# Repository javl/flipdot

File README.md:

### Work in progress! This project is not completed yet!

# Flipdot
A controller for flipdot displays using the FP2800A BROSE chip. The schematic is heavily based on / pretty much a clone of [flippie](https://github.com/545ch4/flippie). See the flippie repo for a great explaination of how the BROSE displays are controlled.

Changes I have made / are planning on making are:

  * [X] Made in the open source Kicad instead of Eagle
  * [X] Replaced the TBD62783A which a A2982 as it seams easier to find
  * [ ] On-board power conversion instead of needing separate inputs for 3.3V, 5V and 24V

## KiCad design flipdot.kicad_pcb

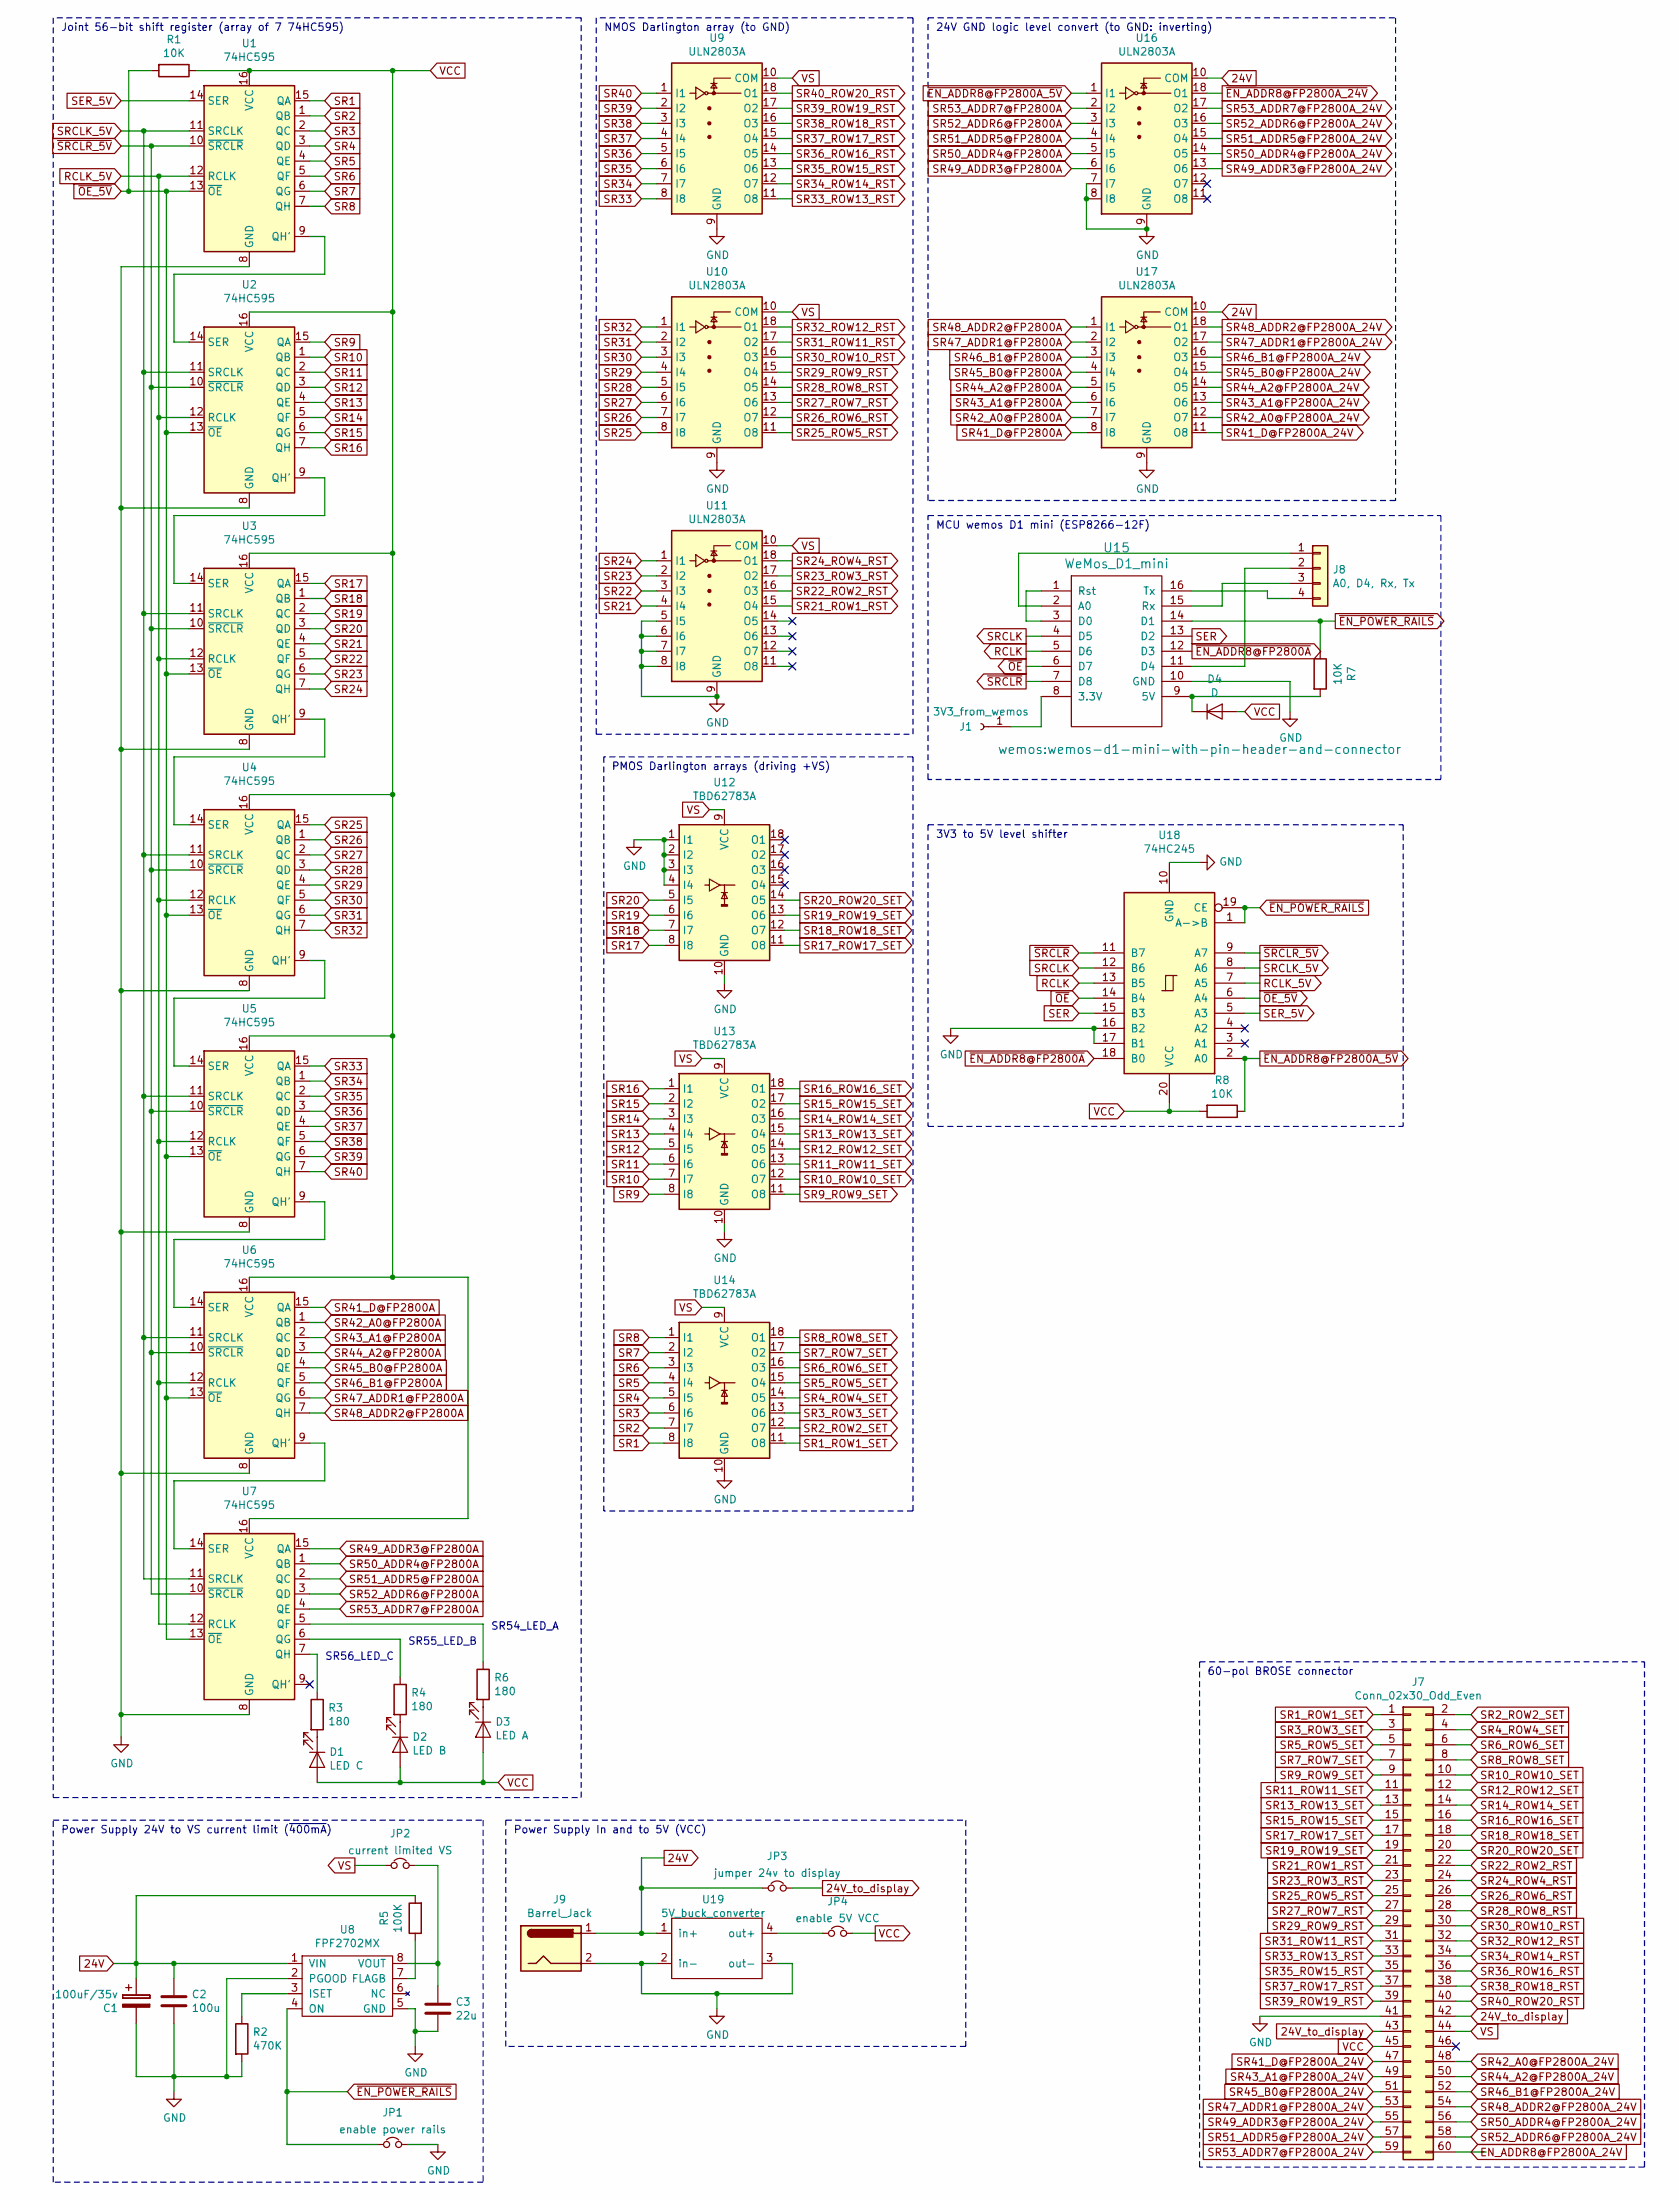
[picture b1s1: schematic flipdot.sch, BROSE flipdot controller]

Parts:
C1: 100uF/35v; CP_Elec_6.3x7.7
C2: 100u; CP_Radial_D6.3mm_P2.50mm
C3: 22u; CP_Radial_D5.0mm_P2.00mm
D1: LED C; LED_0805_2012Metric
D2: LED B; LED_0805_2012Metric
D3: LED A; LED_0805_2012Metric
D4: D; D_A-405_P7.62mm_Horizontal
J1: 3V3_from_wemos; PinHeader_1x01_P2.54mm_Vertical
J7: Conn_02x30_Odd_Even; PinHeader_2x30_P2.54mm_Vertical
J8: A0, D4, Rx, Tx; PinHeader_1x04_P2.54mm_Vertical
J9: Barrel_Jack; BarrelJack_Wuerth_6941xx301002
JP1: enable power rails; PinHeader_1x02_P2.54mm_Vertical
JP2: current limited VS; PinHeader_1x02_P2.54mm_Vertical
JP3: jumper 24v to display; PinHeader_1x02_P2.54mm_Vertical
JP4: enable 5V VCC; PinHeader_1x02_P2.54mm_Vertical
R1, R7, R8: 10K; R_0805_2012Metric
R2: 470K; R_0603_1608Metric
R3, R4, R6: 180; R_0603_1608Metric
R5: 100K; R_0603_1608Metric
U1, U2, U3, U4, U5, U6, U7: 74HC595; SOIC-16_3.9x9.9mm_P1.27mm
U8: FPF2702MX; SOIC-8_3.9x4.9mm_P1.27mm
U9, U10, U11, U16, U17: ULN2803A; SOIC-18W_7.5x11.6mm_P1.27mm
U12, U13, U14: TBD62783A; SOIC-20W_7.5x12.8mm_P1.27mm
U15: WeMos_D1_mini; wemos-d1-mini-with-pin-header-and-connector
U18: 74HC245; SO-20_12.8x7.5mm_P1.27mm
U19: 5V_buck_converter; 5v_buck_converter

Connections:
24V: C1.1, C2.1, J9.1, JP3.1, R5.2, U8.1 (VIN), U16.10 (COM), U17.10 (COM), U19.1 (in+)
24V_to_display: J7.42, J7.43, JP3.2
unnamed: C3.1, JP2.2, U8.8 (VOUT)
unnamed: D1.1 (K), R3.2
unnamed: D2.1 (K), R4.2
unnamed: D3.1 (K), R6.2
unnamed: D4.1 (K), R7.2, U15.9 (5V)
unnamed: J1.1, U15.8 (3.3V)
unnamed: J8.1, U15.2 (A0)
unnamed: J8.2, U15.11 (D4)
unnamed: J8.3, U15.15 (Rx)
unnamed: J8.4, U15.16 (Tx)
unnamed: JP4.1, U19.4 (out+)
unnamed: R2.1, U8.3 (ISET)
unnamed: R3.1, U7.7 (QH)
unnamed: R4.1, U7.6 (QG)
unnamed: R5.1, U8.7 (FLAGB)
unnamed: R6.1, U7.5 (QF)
unnamed: U1.9 (QH'), U2.14 (SER)
unnamed: U2.9 (QH'), U3.14 (SER)
unnamed: U3.9 (QH'), U4.14 (SER)
unnamed: U4.9 (QH'), U5.14 (SER)
unnamed: U5.9 (QH'), U6.14 (SER)
unnamed: U6.9 (QH'), U7.14 (SER)
unnamed: U15.1 (Rst), U15.3 (D0)
RCLK: U15.5 (D6), U18.13 (B5)
RCLK_5V: U1.12 (RCLK), U2.12 (RCLK), U3.12 (RCLK), U4.12 (RCLK), U5.12 (RCLK), U6.12 (RCLK), U7.12 (RCLK), U18.7 (A5)
SER: U15.13 (D2), U18.15 (B3)
SER_5V: U1.14 (SER), U18.5 (A3)
SR1: U1.15 (QA), U14.8 (I8)
SR1_ROW1_SET: J7.1, U14.11 (O8)
SR2: U1.1 (QB), U14.7 (I7)
SR2_ROW2_SET: J7.2, U14.12 (O7)
SR3: U1.2 (QC), U14.6 (I6)
SR3_ROW3_SET: J7.3, U14.13 (O6)
SR4: U1.3 (QD), U14.5 (I5)
SR4_ROW4_SET: J7.4, U14.14 (O5)
SR5: U1.4 (QE), U14.4 (I4)
SR5_ROW5_SET: J7.5, U14.15 (O4)
SR6: U1.5 (QF), U14.3 (I3)
SR6_ROW6_SET: J7.6, U14.16 (O3)
SR7: U1.6 (QG), U14.2 (I2)
SR7_ROW7_SET: J7.7, U14.17 (O2)
SR8: U1.7 (QH), U14.1 (I1)
SR8_ROW8_SET: J7.8, U14.18 (O1)
SR9: U2.15 (QA), U13.8 (I8)
SR9_ROW9_SET: J7.9, U13.11 (O8)
SR10: U2.1 (QB), U13.7 (I7)
SR10_ROW10_SET: J7.10, U13.12 (O7)
SR11: U2.2 (QC), U13.6 (I6)
SR11_ROW11_SET: J7.11, U13.13 (O6)
SR12: U2.3 (QD), U13.5 (I5)
SR12_ROW12_SET: J7.12, U13.14 (O5)
SR13: U2.4 (QE), U13.4 (I4)
SR13_ROW13_SET: J7.13, U13.15 (O4)
SR14: U2.5 (QF), U13.3 (I3)
SR14_ROW14_SET: J7.14, U13.16 (O3)
SR15: U2.6 (QG), U13.2 (I2)
SR15_ROW15_SET: J7.15, U13.17 (O2)
SR16: U2.7 (QH), U13.1 (I1)
SR16_ROW16_SET: J7.16, U13.18 (O1)
SR17: U3.15 (QA), U12.8 (I8)
SR17_ROW17_SET: J7.17, U12.11 (O8)
SR18: U3.1 (QB), U12.7 (I7)
SR18_ROW18_SET: J7.18, U12.12 (O7)
SR19: U3.2 (QC), U12.6 (I6)
SR19_ROW19_SET: J7.19, U12.13 (O6)
SR20: U3.3 (QD), U12.5 (I5)
SR20_ROW20_SET: J7.20, U12.14 (O5)
SR21: U3.4 (QE), U11.4 (I4)
SR21_ROW1_RST: J7.21, U11.15 (O4)
SR22: U3.5 (QF), U11.3 (I3)
SR22_ROW2_RST: J7.22, U11.16 (O3)
SR23: U3.6 (QG), U11.2 (I2)
SR23_ROW3_RST: J7.23, U11.17 (O2)
SR24: U3.7 (QH), U11.1 (I1)
SR24_ROW4_RST: J7.24, U11.18 (O1)
SR25: U4.15 (QA), U10.8 (I8)
SR25_ROW5_RST: J7.25, U10.11 (O8)
SR26: U4.1 (QB), U10.7 (I7)
SR26_ROW6_RST: J7.26, U10.12 (O7)
SR27: U4.2 (QC), U10.6 (I6)
SR27_ROW7_RST: J7.27, U10.13 (O6)
SR28: U4.3 (QD), U10.5 (I5)
SR28_ROW8_RST: J7.28, U10.14 (O5)
SR29: U4.4 (QE), U10.4 (I4)
SR29_ROW9_RST: J7.29, U10.15 (O4)
SR30: U4.5 (QF), U10.3 (I3)
SR30_ROW10_RST: J7.30, U10.16 (O3)
SR31: U4.6 (QG), U10.2 (I2)
SR31_ROW11_RST: J7.31, U10.17 (O2)
SR32: U4.7 (QH), U10.1 (I1)
SR32_ROW12_RST: J7.32, U10.18 (O1)
SR33: U5.15 (QA), U9.8 (I8)
SR33_ROW13_RST: J7.33, U9.11 (O8)
SR34: U5.1 (QB), U9.7 (I7)
SR34_ROW14_RST: J7.34, U9.12 (O7)
SR35: U5.2 (QC), U9.6 (I6)
SR35_ROW15_RST: J7.35, U9.13 (O6)
SR36: U5.3 (QD), U9.5 (I5)
SR36_ROW16_RST: J7.36, U9.14 (O5)
SR37: U5.4 (QE), U9.4 (I4)
SR37_ROW17_RST: J7.37, U9.15 (O4)
SR38: U5.5 (QF), U9.3 (I3)
SR38_ROW18_RST: J7.38, U9.16 (O3)
SR39: U5.6 (QG), U9.2 (I2)
SR39_ROW19_RST: J7.39, U9.17 (O2)
SR40: U5.7 (QH), U9.1 (I1)
SR40_ROW20_RST: J7.40, U9.18 (O1)
SR41_D@FP2800A: U6.15 (QA), U17.8 (I8)
SR41_D@FP2800A_24V: J7.47, U17.11 (O8)
SR42_A0@FP2800A: U6.1 (QB), U17.7 (I7)
SR42_A0@FP2800A_24V: J7.48, U17.12 (O7)
SR43_A1@FP2800A: U6.2 (QC), U17.6 (I6)
SR43_A1@FP2800A_24V: J7.49, U17.13 (O6)
SR44_A2@FP2800A: U6.3 (QD), U17.5 (I5)
SR44_A2@FP2800A_24V: J7.50, U17.14 (O5)
SR45_B0@FP2800A: U6.4 (QE), U17.4 (I4)
SR45_B0@FP2800A_24V: J7.51, U17.15 (O4)
SR46_B1@FP2800A: U6.5 (QF), U17.3 (I3)
SR46_B1@FP2800A_24V: J7.52, U17.16 (O3)
SR47_ADDR1@FP2800A: U6.6 (QG), U17.2 (I2)
SR47_ADDR1@FP2800A_24V: J7.53, U17.17 (O2)
SR48_ADDR2@FP2800A: U6.7 (QH), U17.1 (I1)
SR48_ADDR2@FP2800A_24V: J7.54, U17.18 (O1)
SR49_ADDR3@FP2800A: U7.15 (QA), U16.6 (I6)
SR49_ADDR3@FP2800A_24V: J7.55, U16.13 (O6)
SR50_ADDR4@FP2800A: U7.1 (QB), U16.5 (I5)
SR50_ADDR4@FP2800A_24V: J7.56, U16.14 (O5)
SR51_ADDR5@FP2800A: U7.2 (QC), U16.4 (I4)
SR51_ADDR5@FP2800A_24V: J7.57, U16.15 (O4)
SR52_ADDR6@FP2800A: U7.3 (QD), U16.3 (I3)
SR52_ADDR6@FP2800A_24V: J7.58, U16.16 (O3)
SR53_ADDR7@FP2800A: U7.4 (QE), U16.2 (I2)
SR53_ADDR7@FP2800A_24V: J7.59, U16.17 (O2)
SRCLK: U15.4 (D5), U18.12 (B6)
SRCLK_5V: U1.11 (SRCLK), U2.11 (SRCLK), U3.11 (SRCLK), U4.11 (SRCLK), U5.11 (SRCLK), U6.11 (SRCLK), U7.11 (SRCLK), U18.8 (A6)
VCC: D1.2 (A), D2.2 (A), D3.2 (A), D4.2 (A), J7.45, JP4.2, R1.1, R8.2, U1.16 (VCC), U2.16 (VCC), U3.16 (VCC), U4.16 (VCC), U5.16 (VCC), U6.16 (VCC), U7.16 (VCC), U18.20 (VCC)
VS: J7.44, JP2.1, U9.10 (COM), U10.10 (COM), U11.10 (COM), U12.9 (VCC), U13.9 (VCC), U14.9 (VCC)
~EN_ADDR8@FP2800A: U15.12 (D3), U18.18 (B0)
~EN_ADDR8@FP2800A_5V: R8.1, U16.1 (I1), U18.2 (A0)
~EN_POWER_RAILS: JP1.1, R7.1, U8.4 (ON), U15.14 (D1), U18.1 (A->B), U18.19 (CE)
~OE: U15.6 (D7), U18.14 (B4)
~OE_5V: R1.2, U1.13 (~OE), U2.13 (~OE), U3.13 (~OE), U4.13 (~OE), U5.13 (~OE), U6.13 (~OE), U7.13 (~OE), U18.6 (A4)
~SRCLR: U15.7 (D8), U18.11 (B7)
~SRCLR_5V: U1.10 (~SRCLR), U2.10 (~SRCLR), U3.10 (~SRCLR), U4.10 (~SRCLR), U5.10 (~SRCLR), U6.10 (~SRCLR), U7.10 (~SRCLR), U18.9 (A7)

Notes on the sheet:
Joint 56-bit shift register (array of 7 74HC595)
24V GND logic level convert (to GND: inverting)
NMOS Darlington array (to GND)
MCU wemos D1 mini (ESP8266-12F)
Power Supply 24V to VS current limit (~400mA)
PMOS Darlington arrays (driving +VS)
3V3 to 5V level shifter
60-pol BROSE connector
SR54_LED_A
SR55_LED_B
SR56_LED_C
Power Supply In and to 5V (VCC)

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
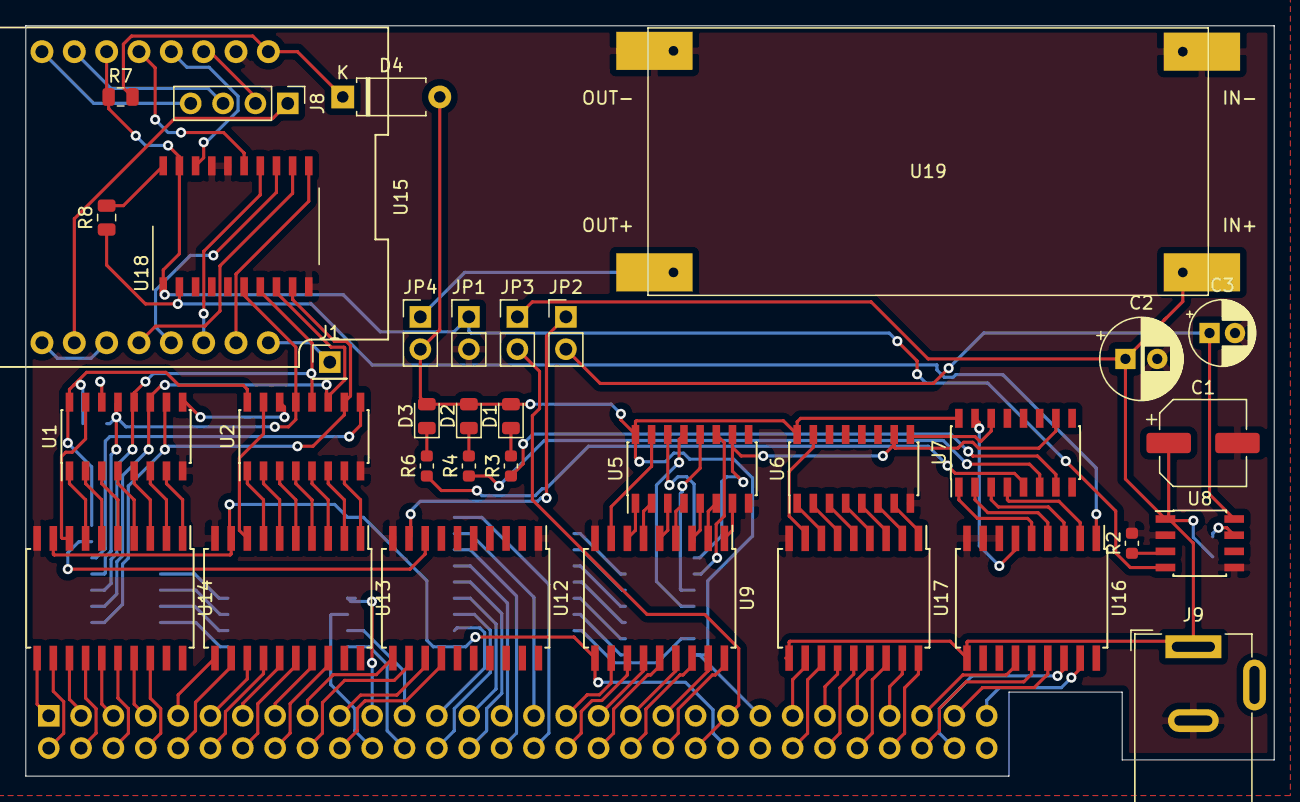
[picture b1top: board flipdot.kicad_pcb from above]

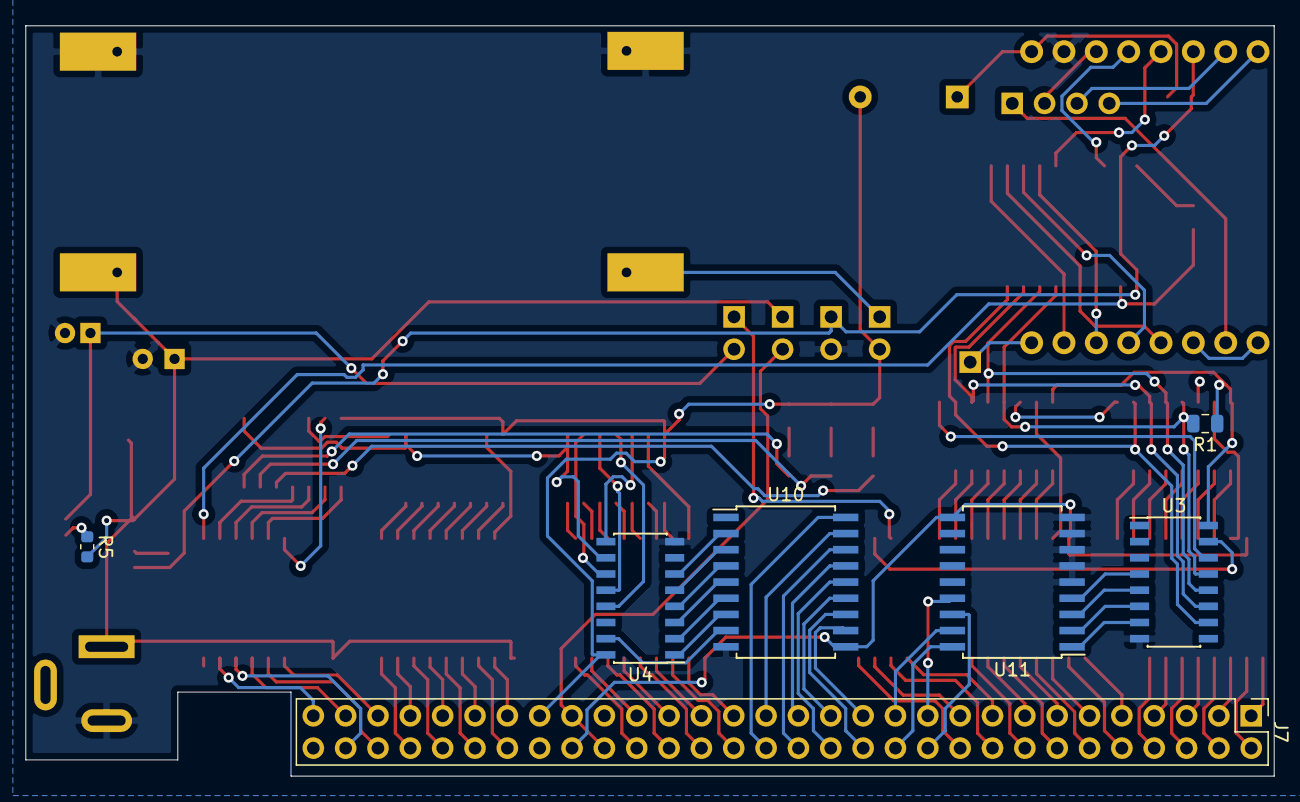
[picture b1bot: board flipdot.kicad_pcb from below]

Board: 2 copper layers, 98.0 x 58.9 mm, 42 parts (7 on the bottom side), 148 nets.

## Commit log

2020-10-12 feature: add basic readme
2020-10-12 update footprints
